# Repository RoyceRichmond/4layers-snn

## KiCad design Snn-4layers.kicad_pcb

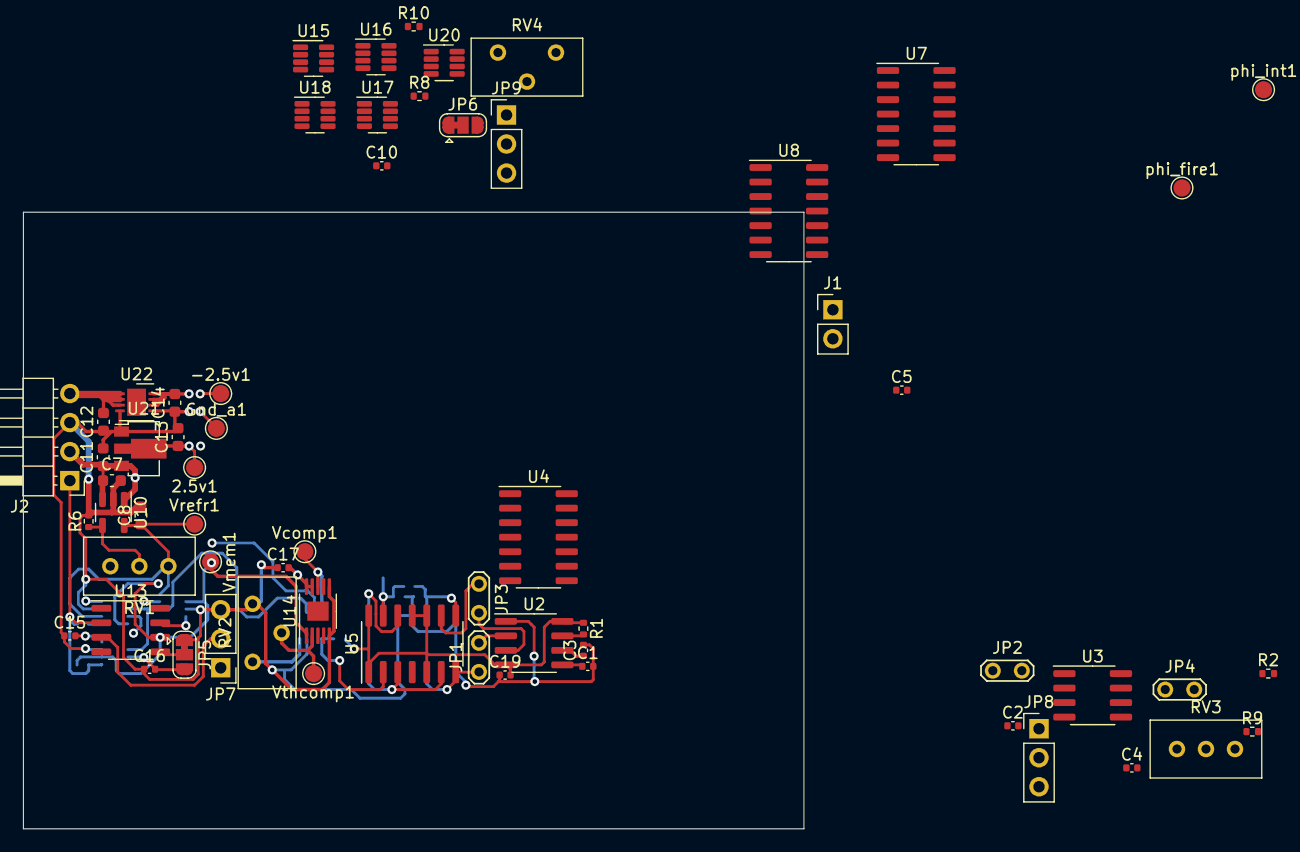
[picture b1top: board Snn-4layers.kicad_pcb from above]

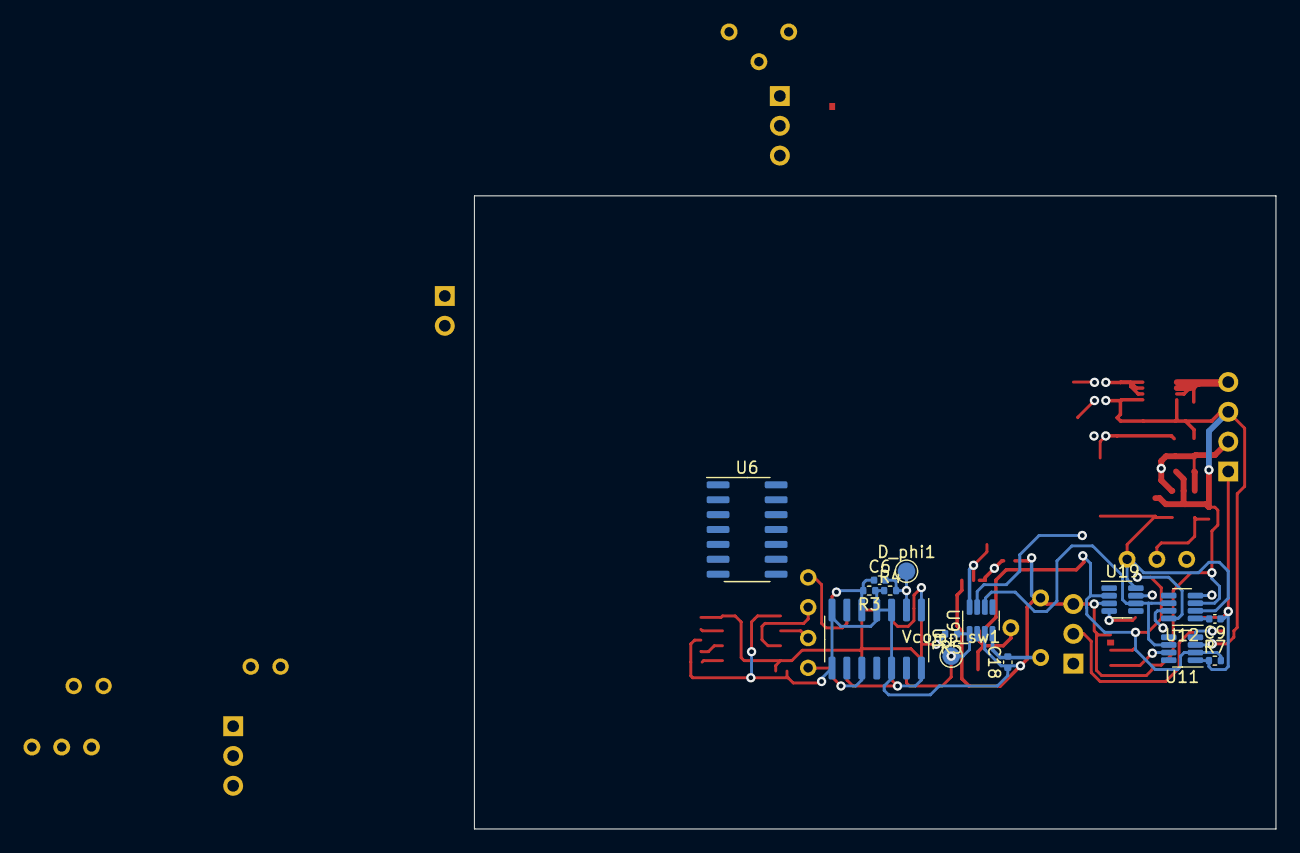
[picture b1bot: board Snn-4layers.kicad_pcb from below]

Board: 4 copper layers, 68.3 x 54.0 mm, 77 parts (15 on the bottom side), 48 nets.

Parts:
2.5v1: TestPoint; TestPoint_Pad_D1.5mm
-2.5v1: TestPoint; TestPoint_Pad_D1.5mm
C1, C2: 0.1u; C_0402_1005Metric
C3: 0.03u; C_0402_1005Metric
C4: 0.25u; C_0402_1005Metric
C5: 1n; C_0402_1005Metric
C6: 10p; C_0402_1005Metric
C7, C8: 1u; C_0603_1608Metric
C9: 20n; C_0402_1005Metric
C10: 500p; C_0402_1005Metric
C11, C12, C14: 10uf; C_0603_1608Metric
C13: 22uf; C_0603_1608Metric
C15, C16, C17, C18, C19: 100n; C_0402_1005Metric
D_phi1: TestPoint; TestPoint_Pad_D1.5mm
Gnd_a1: TestPoint; TestPoint_Pad_D1.5mm
J1: Output connector; PinHeader_1x02_P2.54mm_Vertical
J2: Input connector; PinHeader_1x04_P2.54mm_Horizontal
JP1, JP2, JP3, JP4: Jumper_2_Bridged; TestPoint_2Pads_Pitch2.54mm_Drill0.8mm
JP5, JP6: SolderJumper_3_Bridged12; SolderJumper-3_P1.3mm_Bridged12_RoundedPad1.0x1.5mm
JP7, JP8, JP9: Jumper_3_Bridged12; PinHeader_1x03_P2.54mm_Vertical
R1, R2: 4.7k; R_0402_1005Metric
R3, R6, R10: 10k; R_0402_1005Metric
R4: 1M; R_0402_1005Metric
R5: 109k; R_0402_1005Metric
R7, R8: 500k; R_0402_1005Metric
R9: 330; R_0402_1005Metric
RV1: 20k; Potentiometer_Bourns_3296W_Vertical
RV2: 100k; Potentiometer_Bourns_3296Y_Vertical
RV3: 5k; Potentiometer_Bourns_3296W_Vertical
RV4: 500k; Potentiometer_Bourns_3296Y_Vertical
U1, U6, U8: ALD1106; SOIC-14_3.9x8.7mm_P1.27mm
U2, U3: LM555xM; SOIC-8_3.9x4.9mm_P1.27mm
U4, U5, U7: ALD1107; SOIC-14_3.9x8.7mm_P1.27mm
U9, U11, U12, U15, U16, U17, U18, U19, U20: ADG619; SOT-23-8
U10: AP7366; SOT-23-5
U13: LTC6268xS8-10; SO-8_3.9x4.9mm_P1.27mm
U14: LT1715; MSOP-10-1EP_3x3mm_P0.5mm_EP1.68x1.88mm
U21: AP1117Y25G; SOT-89-3
U22: LT3015EDD-2.5; DFN-8-1EP_3x3mm_P0.5mm_EP1.65x2.38mm
Vcomp1: TestPoint; TestPoint_Pad_D1.5mm
Vcomp_sw1: TestPoint; TestPoint_Pad_D1.5mm
Vmem1: TestPoint; TestPoint_Pad_D1.5mm
Vrefr1: TestPoint; TestPoint_Pad_D1.5mm
Vthcomp1: TestPoint; TestPoint_Pad_D1.5mm
phi_fire1: TestPoint; TestPoint_Pad_D1.5mm
phi_int1: TestPoint; TestPoint_Pad_D1.5mm

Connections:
+2V5: 2.5v1.1, C13.1, C15.2, C18.2, RV2.3, U9.4 (vdd), U11.4 (vdd), U12.4 (vdd), U13.7 (V+), U15.1 (D), U15.4 (vdd), U16.4 (vdd), U17.4 (vdd), U18.4 (vdd), U19.4 (vdd), U20.4 (vdd), U21.2 (VO)
+5V: C7.1, C11.1, C17.2, C19.2, J2.2, R1.1, R2.1, R5.2, R9.1, U2.4 (R), U2.8 (VCC), U3.4 (R), U3.8 (VCC), U4.1 (D), U4.5 (D), U4.10 (D), U4.11 (V+), U5.1 (D), U5.5 (D), U5.10 (D), U5.11 (V+), U5.14 (D), U7.1 (D), U7.11 (V+), U10.1 (IN), U10.3 (EN), U14.9 (+V_{s}), U14.10 (V_{CC}), U21.3 (VI)
-2V5: -2.5v1.1, C14.2, C16.2, JP5.3 (B), JP6.3 (B), U9.7 (vss), U11.7 (vss), U12.7 (vss), U15.7 (vss), U16.7 (vss), U17.7 (vss), U18.7 (vss), U19.7 (vss), U20.7 (vss), U22.6 (SENSE), U22.7 (OUT), U22.8 (OUT)
-5V: C12.2, J2.4, U22.1 (IN), U22.2 (IN), U22.3 (~SHDN)
GND: C1.2, C2.2, C3.2, C4.2, C5.2, C7.2, C8.2, C10.1, C11.2, C12.1, C13.2, C14.1, C15.1, C16.1, C17.1, C18.1, C19.1, Gnd_a1.1, J1.1, J2.3, JP5.1 (A), JP6.1 (A), JP7.3 (B), R3.1, R4.1, R6.2, RV2.1, U1.3 (S), U1.4 (V-), U1.7 (S), U1.8 (S), U1.12 (S), U2.1 (GND), U3.1 (GND), U6.3 (S), U6.4 (V-), U6.7 (S), U6.8 (S), U6.12 (S), U8.3 (S), U8.4 (V-), U9.3 (gnd), U10.2 (GND), U11.3 (gnd), U12.3 (gnd), U14.5 (V_{EE}), U14.6 (gnd), U15.3 (gnd), U16.3 (gnd), U17.3 (gnd), U18.3 (gnd), U19.3 (gnd), U20.3 (gnd), U21.1 (GND), U22.4 (GND), U22.5 (GND)
I_in: C9.1, J2.1, R7.1, U11.1 (D), U13.2 (-)
unnamed: C1.1, U2.5 (CV)
unnamed: C2.1, U3.5 (CV)
unnamed: C3.1, U2.6 (THR)
unnamed: C4.1, U3.6 (THR)
unnamed: C9.2, U12.1 (D)
unnamed: C10.2, JP9.2 (C), U17.2 (S1), U20.1 (D)
unnamed: JP1.2 (B), U2.2 (TR)
unnamed: JP2.2 (B), U3.2 (TR)
unnamed: JP3.2 (B), U2.3 (Q)
unnamed: JP4.2 (B), U3.3 (Q)
unnamed: JP5.2 (C), U13.5 (V-)
unnamed: JP6.2 (C), U17.1 (D)
unnamed: JP7.1 (A), U15.2 (S1), U16.2 (S1), U20.2 (S1)
unnamed: JP7.2 (C), U13.3 (+)
unnamed: JP8.1 (A), R2.2
unnamed: JP8.2 (C), U3.7 (DIS)
unnamed: JP8.3 (B), RV3.1
unnamed: JP9.1 (A), R8.2
unnamed: JP9.3 (B), RV4.2
unnamed: R1.2, U2.7 (DIS)
unnamed: R6.1, RV1.2, U10.4 (ADJ)
unnamed: R7.2, U11.2 (S1), U12.8 (S2), U13.6, U14.1 (+), U19.2 (S1), Vmem1.1
unnamed: R9.2, RV3.2
unnamed: R8.1, R10.1, U18.2 (S1)
unnamed: R10.2, RV4.3
unnamed: RV2.2, U14.2 (-), Vthcomp1.1
unnamed: U1.1 (D), U4.2 (G), U5.12 (S), U6.13 (G)
unnamed: U1.9 (G), U1.14 (D), U5.3 (S), U5.6 (G)
unnamed: U4.3 (S), U4.6 (G), U6.9 (G), U6.14 (D)
unnamed: U4.8 (S), U4.14 (D)
d_phi1: C6.2, D_phi1.1, R4.2, U1.2 (G), U5.13 (G)
n_phi1: C6.1, R3.2, U1.5 (D), U5.8 (S)
phi1: JP3.1 (A), U1.6 (G), U4.9 (G), U5.9 (G), U6.6 (G), U15.6 (IN), U17.6 (IN)
phi2: JP4.1 (A), U4.13 (G), U6.2 (G), U18.6 (IN), U20.6 (IN)
phi_fire: U7.3 (S), U8.1 (D), U9.6 (IN), U11.6 (IN), U12.6 (IN), U19.6 (IN), phi_fire1.1
phi_int: C5.1, U4.12 (S), U6.1 (D), U6.5 (D), U7.2 (G), U8.2 (G), U16.6 (IN), phi_int1.1
trig1: JP1.1 (A), U1.10 (D), U5.7 (S)
trig2: JP2.1 (A), U4.7 (S), U6.10 (D)
vcomp: U9.8 (S2), U14.8 (Q), Vcomp1.1
vcomp_sw: R5.1, U1.13 (G), U5.2 (G), U9.1 (D), Vcomp_sw1.1
vout: J1.2, U19.1 (D)
vrefr: C8.1, RV1.3, U10.5 (OUT), U12.2 (S1), U16.1 (D), U18.1 (D), U19.8 (S2), Vrefr1.1

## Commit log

2022-09-17 4layer supplies wired up
2022-09-17 4layer first cmos connected
2022-09-17 semi final design
2022-09-17 added redundacy for the schematic
